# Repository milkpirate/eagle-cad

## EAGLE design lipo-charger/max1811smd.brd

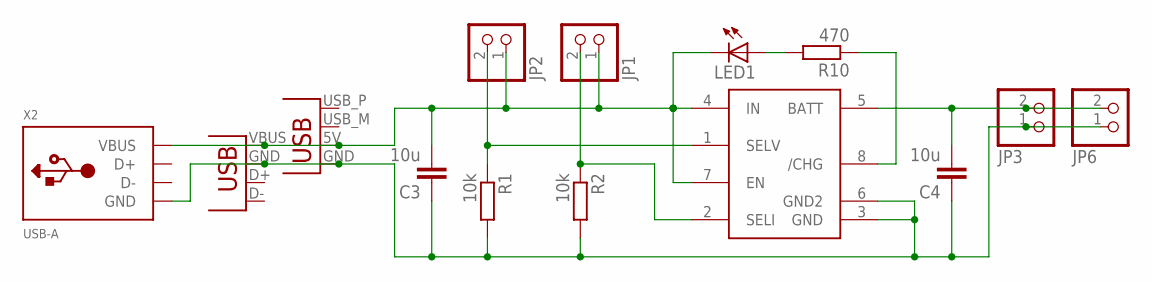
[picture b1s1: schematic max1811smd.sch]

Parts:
C3, C4: 10u; C0805K
CN1: USBPCB; USB-A-PCB
JP1, JP2, JP3, JP6: PINHD-1X2; 1X02
LED1: LEDCHIPLED_0805; CHIPLED_0805
R1, R2: 10k; M0805
R10: 470; M0805
U$1: MAX1811SO8; SO08
X1: USB-A-H
X2: USB-A; MOLEX_480371000

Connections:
unnamed: C3.1, C4.1, CN1.GND, JP3.1, JP6.1, R1.2, R2.2, U$1.3 (GND), U$1.6 (GND2), X1.GND (VBUS), X2.4 (GND)
unnamed: JP1.2, R2.1, U$1.2 (SELI)
unnamed: JP2.2, R1.1, U$1.1 (SELV)
unnamed: R10.1, U$1.8 (/CHG)
unnamed: LED1.A, R10.2
unnamed: C4.2, JP3.2, JP6.2, U$1.5 (BATT)
unnamed: C3.2, CN1.5V (VBUS), JP1.1, JP2.1, LED1.C, U$1.4 (IN), U$1.7 (EN), X1.VBUS (GND), X2.1 (VBUS)

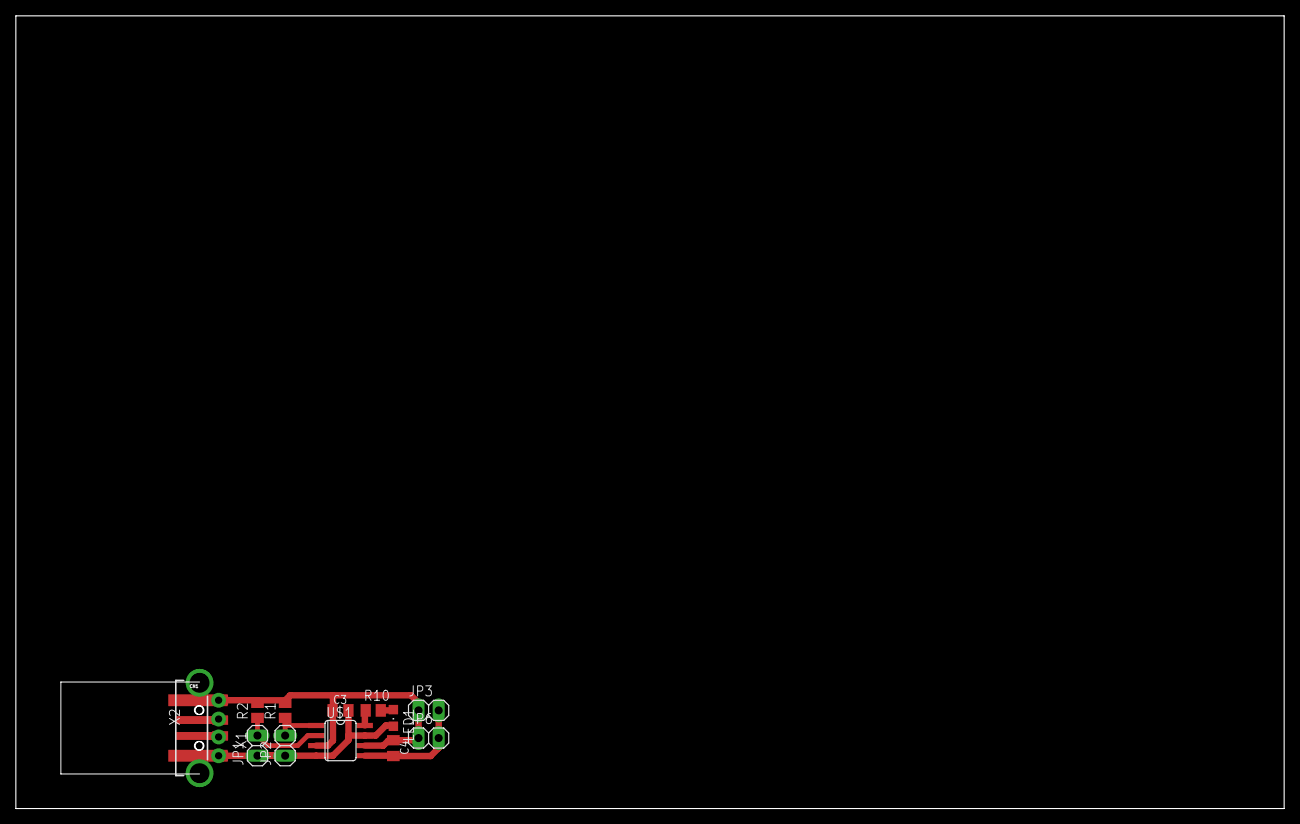
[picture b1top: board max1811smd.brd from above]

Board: 2 copper layers, 160.0 x 100.0 mm, 14 parts (0 on the bottom side), 7 nets.

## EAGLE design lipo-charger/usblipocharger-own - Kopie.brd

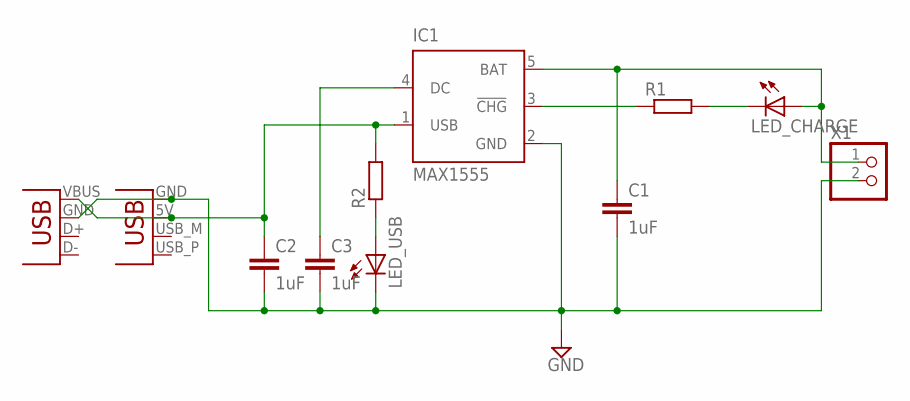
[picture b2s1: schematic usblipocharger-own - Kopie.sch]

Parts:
C1, C2, C3: 1uF; C0805
IC1: MAX1555; SOT23-5L
JP1: USBPCB; USB-A-PCB
JP2: USB-A-H
LED_CHARGE: LEDCHIP-LED0805; CHIP-LED0805
LED_USB: LEDCHIP-LED0805; CHIP-LED0805
R1, R2: R-EU_R0805; R0805
X1: PINHD-1X2; 1X02

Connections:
GND: C1.2, C2.2, C3.2, IC1.2 (GND), JP1.GND, JP2.GND (VBUS), LED_USB.C, X1.2
LIPO+: C1.1, IC1.5 (BAT), LED_CHARGE.A, X1.1
unnamed: LED_USB.A, R2.1
unnamed: C2.1, IC1.1 (USB), JP1.5V (VBUS), JP2.VBUS (GND), R2.2
unnamed: C3.1, IC1.4 (DC)
unnamed: IC1.3 (!CHG), R1.1
unnamed: LED_CHARGE.C, R1.2

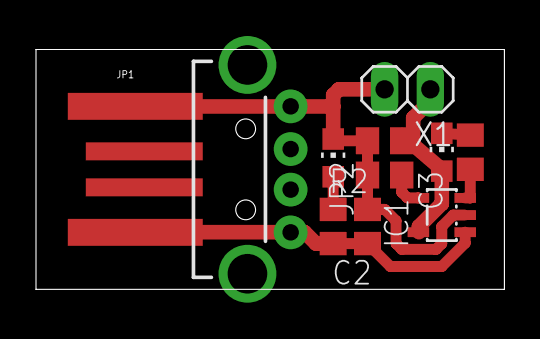
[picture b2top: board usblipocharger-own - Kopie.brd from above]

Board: 2 copper layers, 26.0 x 13.3 mm, 11 parts (0 on the bottom side), 7 nets.

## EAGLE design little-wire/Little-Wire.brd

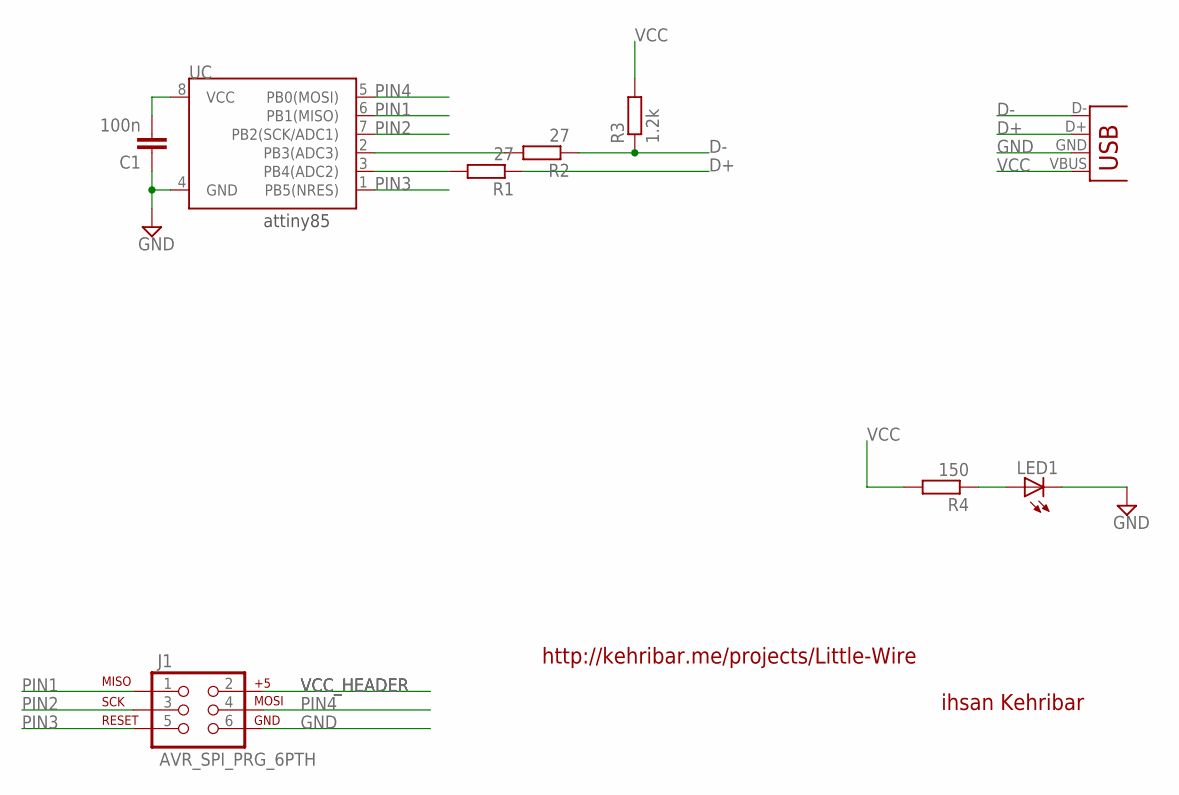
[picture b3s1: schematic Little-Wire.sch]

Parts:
C1: 100n; C025-025X050
J1: AVR_SPI_PRG_6PTH; 2X3
LED1: LED3MM
R1, R2: 27; 0204/5
R3: 1.2k; 0204/5
R4: 150; 0204/5
UC: ATTINY45DIP8; DIP08
X1: USB-A-H

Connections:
D+: R1.1, X1.D+ (D-)
D-: R2.1, R3.1, X1.D- (D+)
GND: C1.1, J1.6, LED1.K (C), UC.4 (GND), X1.GND (VBUS)
unnamed: R2.2, UC.2 (PB3(ADC3))
unnamed: R1.2, UC.3 (PB4(ADC2))
unnamed: LED1.A, R4.1
PIN1: J1.1, UC.6 (PB1(MISO))
PIN2: J1.3, UC.7 (PB2(SCK/ADC1))
PIN3: J1.5, UC.1 (PB5(NRES))
PIN4: J1.4, UC.5 (PB0(MOSI))
VCC: C1.2, R3.2, R4.2, UC.8 (VCC), X1.VBUS (GND)
VCC_HEADER: J1.2

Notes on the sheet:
attiny85
http://kehribar.me/projects/Little-Wire
ihsan Kehribar

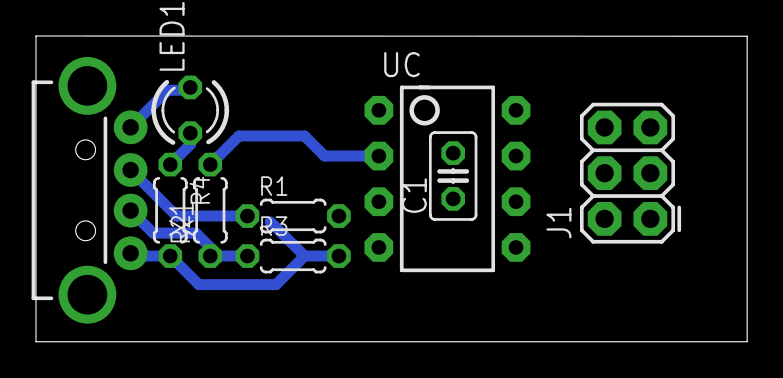
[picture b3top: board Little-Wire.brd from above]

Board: 2 copper layers, 39.5 x 17.0 mm, 9 parts (0 on the bottom side), 11 nets.

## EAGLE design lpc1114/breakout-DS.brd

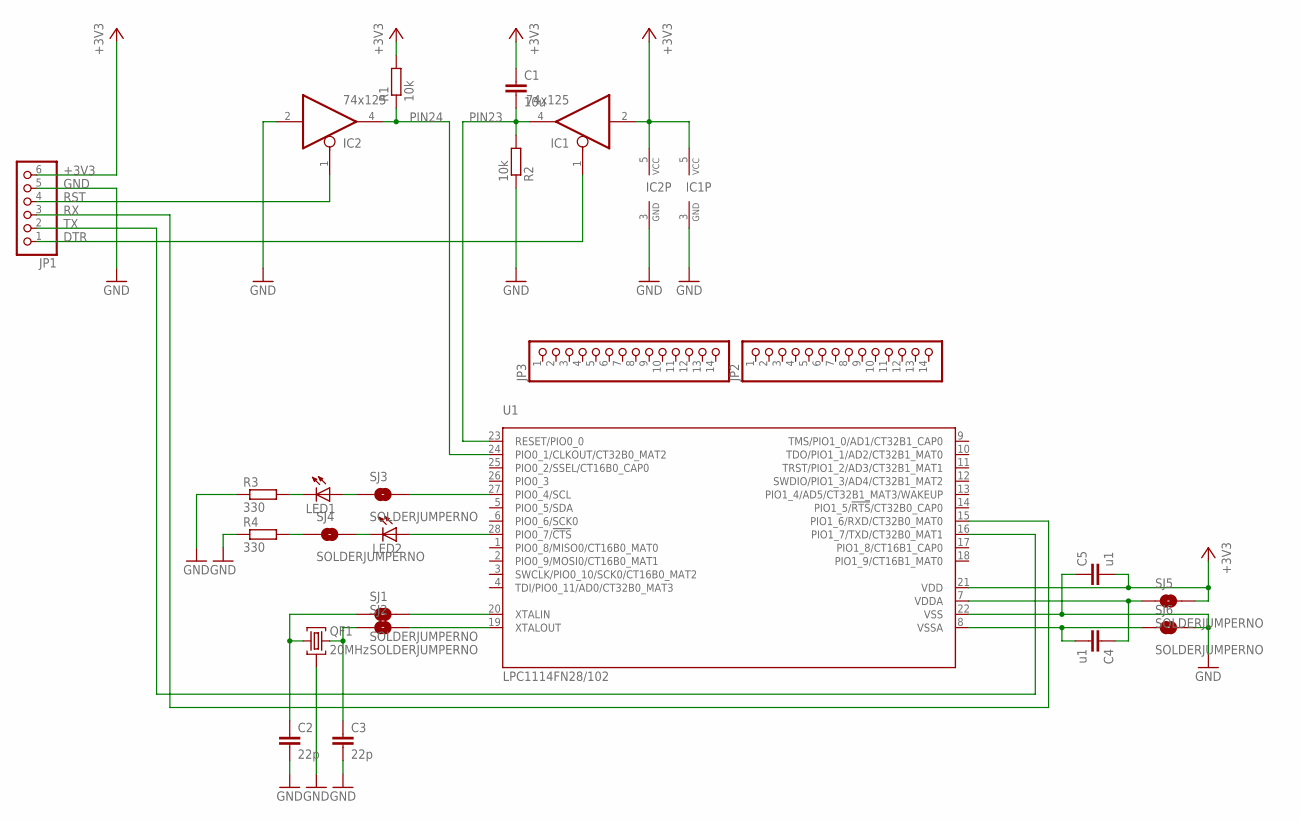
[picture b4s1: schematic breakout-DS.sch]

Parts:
C1: 10u; C0805K
C2, C3: 22p; C0805K
C4, C5: u1; C0805K
IC1, IC2: 74x125; SOT23-5
JP1: PINHD-1X6/90; 1X06/90
JP2, JP3: PINHD-1X14; 1X14
LED1, LED2: LEDLD260; LD260
QF1: 20MHz; HC49U
R1, R2: 10k; M0805
R3, R4: 330; M0805
SJ1, SJ2, SJ3, SJ4, SJ5, SJ6: SOLDERJUMPERNO; SJ_2S-NO
U1: LPC1114FN28/102; SOT117

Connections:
+3V3: C1.1, C5.2, IC1.2 (I), IC1.5 (VCC), IC2.5 (VCC), JP1.6, R1.2, SJ5.2, U1.21 (VDD)
DTR: IC1.1 (OE), JP1.1
GND: C2.2, C3.2, C5.1, IC1.3 (GND), IC2.2 (I), IC2.3 (GND), JP1.5, QF1.2, R2.1, R3.1, R4.1, SJ6.2, U1.22 (VSS)
unnamed: LED2.A, U1.28 (PIO0_7/!CTS!)
unnamed: LED1.A, SJ3.1
unnamed: LED1.K (C), R3.2
unnamed: R4.2, SJ4.1
unnamed: SJ2.2, U1.19 (XTALOUT)
unnamed: SJ1.2, U1.20 (XTALIN)
unnamed: LED2.K (C), SJ4.2
unnamed: SJ3.2, U1.27 (PIO0_4/SCL)
unnamed: C3.1, QF1.3, SJ2.1
unnamed: C2.1, QF1.1, SJ1.1
PIN7: C4.1, SJ5.1, U1.7 (VDDA)
PIN8: C4.2, SJ6.1, U1.8 (VSSA)
PIN23: C1.2, IC1.4 (O), R2.2, U1.23 (RESET/PIO0_0)
PIN24: IC2.4 (O), R1.1, U1.24 (PIO0_1/CLKOUT/CT32B0_MAT2)
RST: IC2.1 (OE), JP1.4
RX: JP1.3, U1.15 (PIO1_6/RXD/CT32B0_MAT0)
TX: JP1.2, U1.16 (PIO1_7/TXD/CT32B0_MAT1)

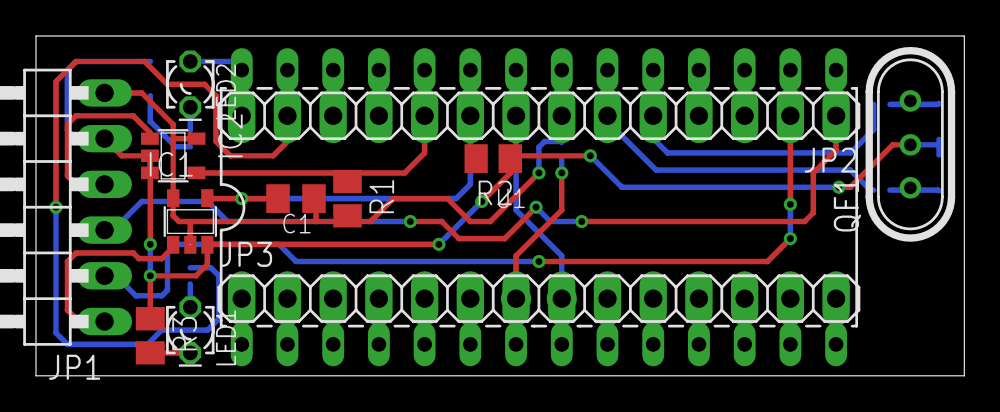
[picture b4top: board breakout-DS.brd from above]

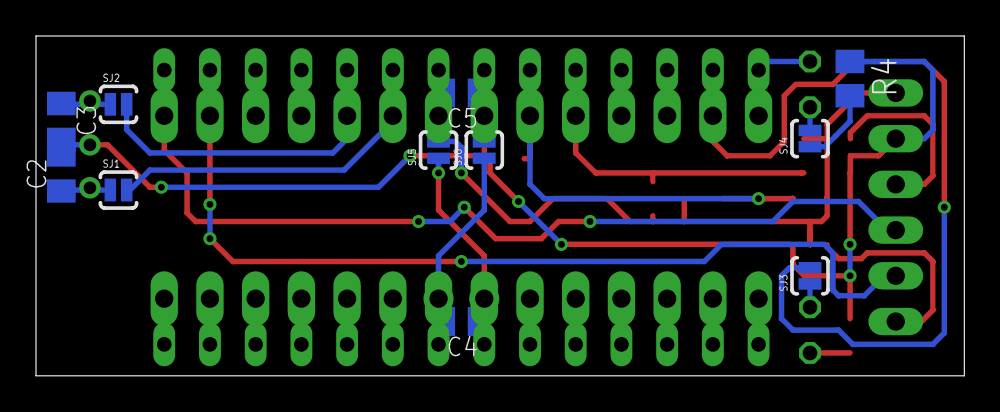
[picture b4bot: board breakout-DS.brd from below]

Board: 2 copper layers, 51.6 x 18.9 mm, 24 parts (11 on the bottom side), 20 nets.

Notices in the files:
parts and their libraries:
SparkFun: Licensing: CC v3.0 Share-Alike You are welcome to use this library for commercial purposes.
